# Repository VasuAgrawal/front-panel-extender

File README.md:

# See the associated blog post on my website [here](https://vasuagrawal.com/2025/05/custom-front-panel-extension-pcb/).

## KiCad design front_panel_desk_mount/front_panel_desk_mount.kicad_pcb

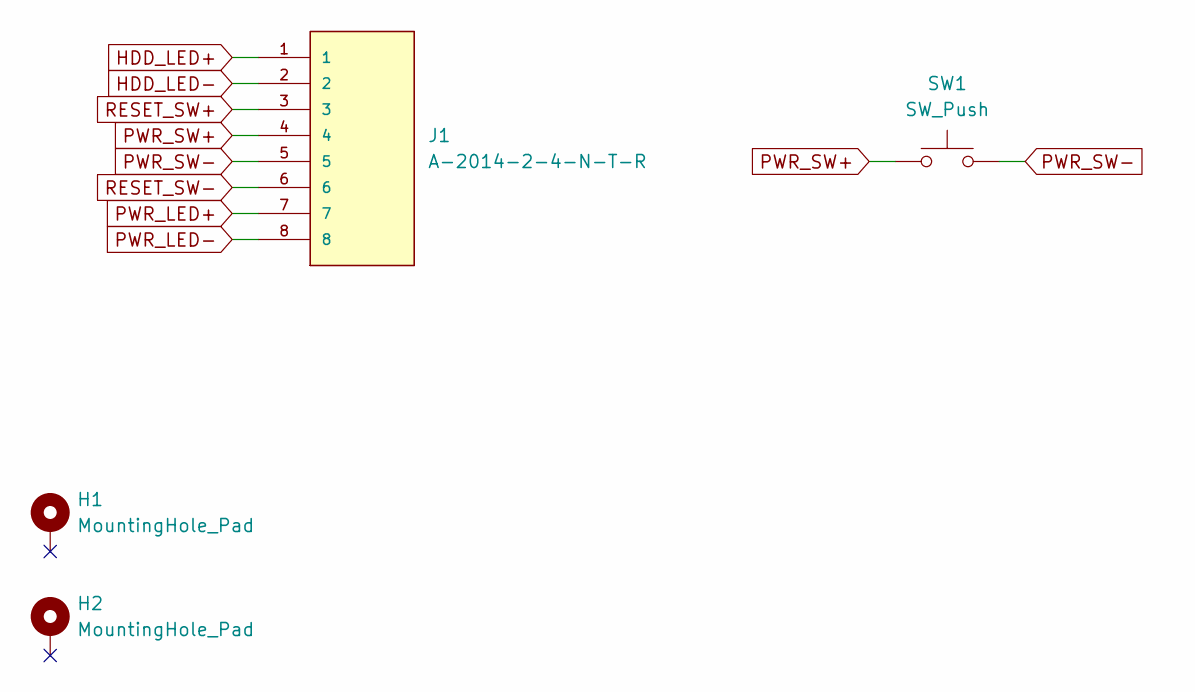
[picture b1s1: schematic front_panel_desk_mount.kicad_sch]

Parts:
H1, H2: MountingHole_Pad; MountingHole_3.2mm_M3_Pad
J1: A-2014-2-4-N-T-R; ASSMANN_A-2014-2-4-N-T-R; PARTREV 01; Digikey AE10396-ND
SW1: SW_Push; SW_Cherry_MX_PCB_1.00u

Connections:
HDD_LED+: J1.1
HDD_LED-: J1.2
PWR_LED+: J1.7
PWR_LED-: J1.8
PWR_SW+: J1.4, SW1.1
PWR_SW-: J1.5, SW1.2
RESET_SW+: J1.3
RESET_SW-: J1.6

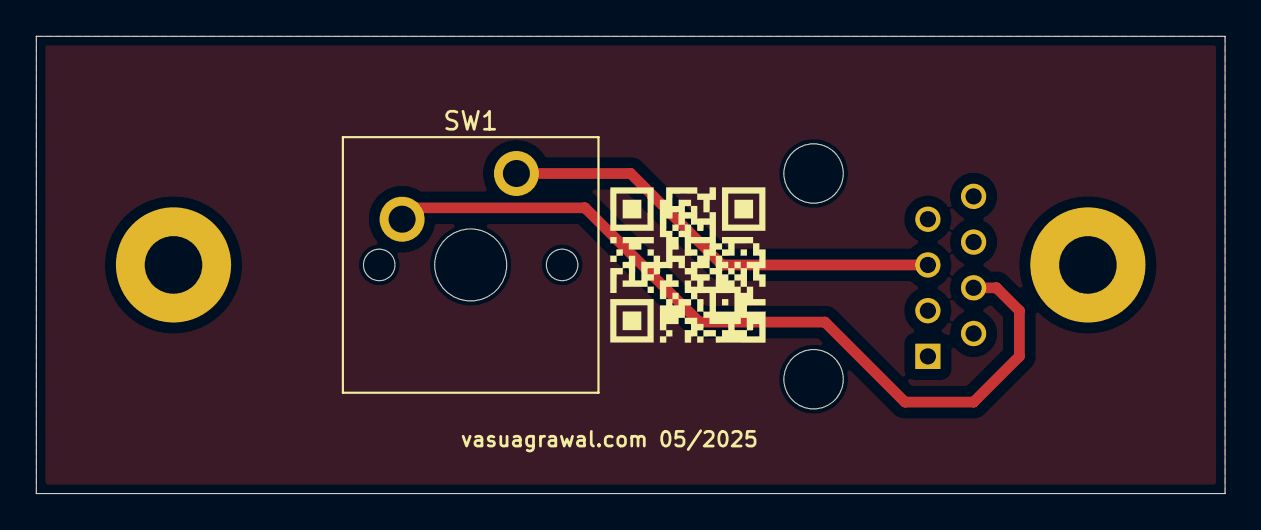
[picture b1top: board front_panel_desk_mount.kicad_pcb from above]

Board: 2 copper layers, 66.0 x 25.4 mm, 4 parts (1 on the bottom side), 2 nets.

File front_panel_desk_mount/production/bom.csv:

Designator,Footprint,Quantity,Value,LCSC Part #
J1,ASSMANN_A-2014-2-4-N-T-R,1,A-2014-2-4-N-T-R,
SW1,SW_Cherry_MX_PCB_1.00u,1,SW_Push,

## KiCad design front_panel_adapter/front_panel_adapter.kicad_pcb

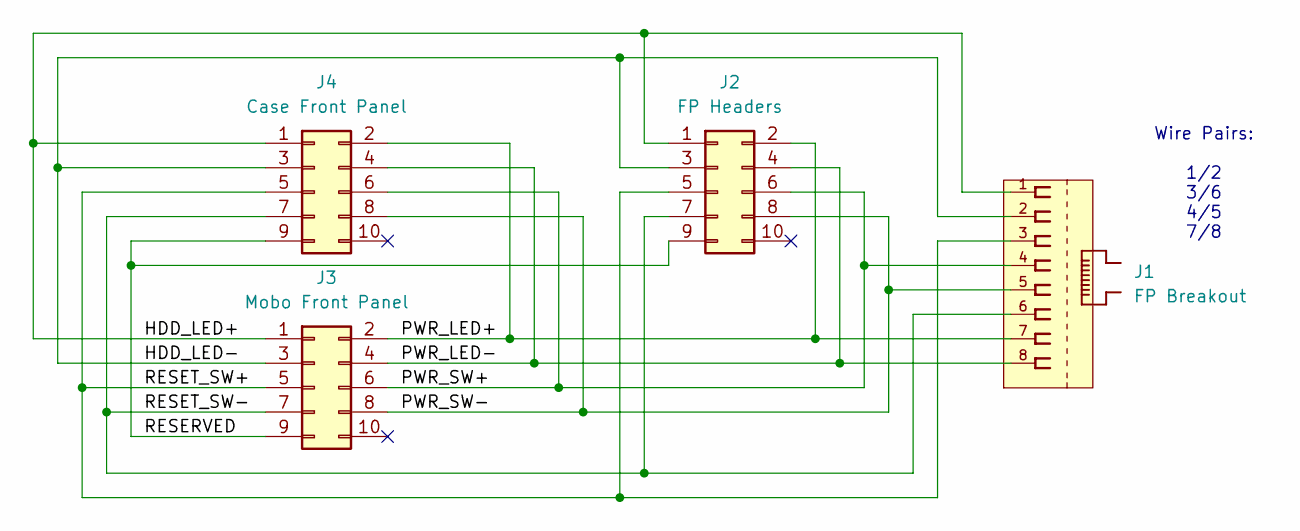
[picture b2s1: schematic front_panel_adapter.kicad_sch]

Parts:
J1: FP Breakout; AMPHENOL_54602-908LF; PARTREV J; DigiKey 609-1046-ND
J2: FP Headers; PinHeader_2x05_P2.54mm_Vertical; DigiKey 1849-1002-ND
J3: Mobo Front Panel; PinSocket_2x05_P2.54mm_Vertical; DigiKey 4324-FHMD-DA010G1NBON-B-ND
J4: Case Front Panel; PinHeader_2x05_P2.54mm_Vertical; DigiKey 1849-1002-ND

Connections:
/HDD_LED+: J1.1, J2.1, J3.1, J4.1
/HDD_LED-: J1.2, J2.3, J3.3, J4.3
/PWR_LED+: J1.7, J2.2, J3.2, J4.2
/PWR_LED-: J1.8, J2.4, J3.4, J4.4
/PWR_SW+: J1.4, J2.6, J3.6, J4.6
/PWR_SW-: J1.5, J2.8, J3.8, J4.8
/RESERVED: J2.9, J3.9, J4.9
/RESET_SW+: J1.3, J2.5, J3.5, J4.5
/RESET_SW-: J1.6, J2.7, J3.7, J4.7

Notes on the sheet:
Wire Pairs: 1/2 3/6 4/5 7/8

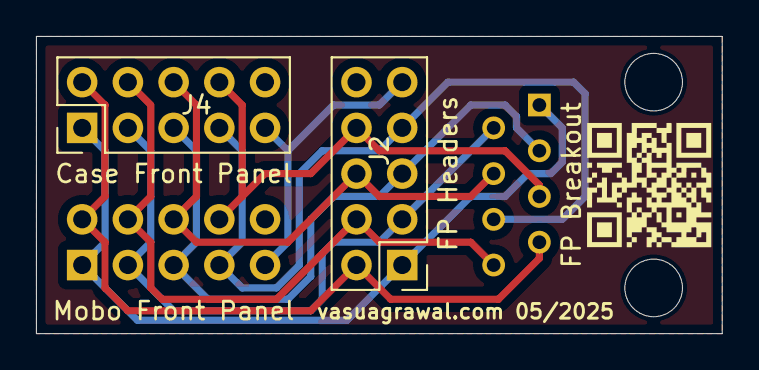
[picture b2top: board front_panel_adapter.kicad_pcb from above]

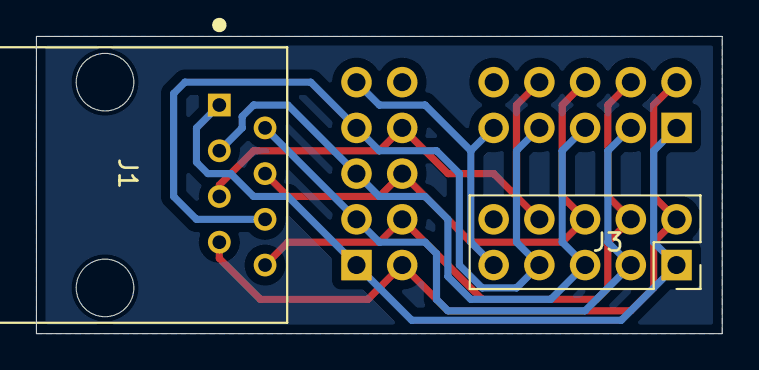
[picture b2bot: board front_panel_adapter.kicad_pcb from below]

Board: 2 copper layers, 38.1 x 16.5 mm, 4 parts (2 on the bottom side), 9 nets.

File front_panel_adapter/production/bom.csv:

Designator,Footprint,Quantity,Value,LCSC Part #
J1,AMPHENOL_54602-908LF,1,FP Breakout,C2847314
J2,PinHeader_2x05_P2.54mm_Vertical,1,FP Headers,
J3,PinSocket_2x05_P2.54mm_Vertical,1,Mobo Front Panel,
J4,PinHeader_2x05_P2.54mm_Vertical,1,Case Front Panel,

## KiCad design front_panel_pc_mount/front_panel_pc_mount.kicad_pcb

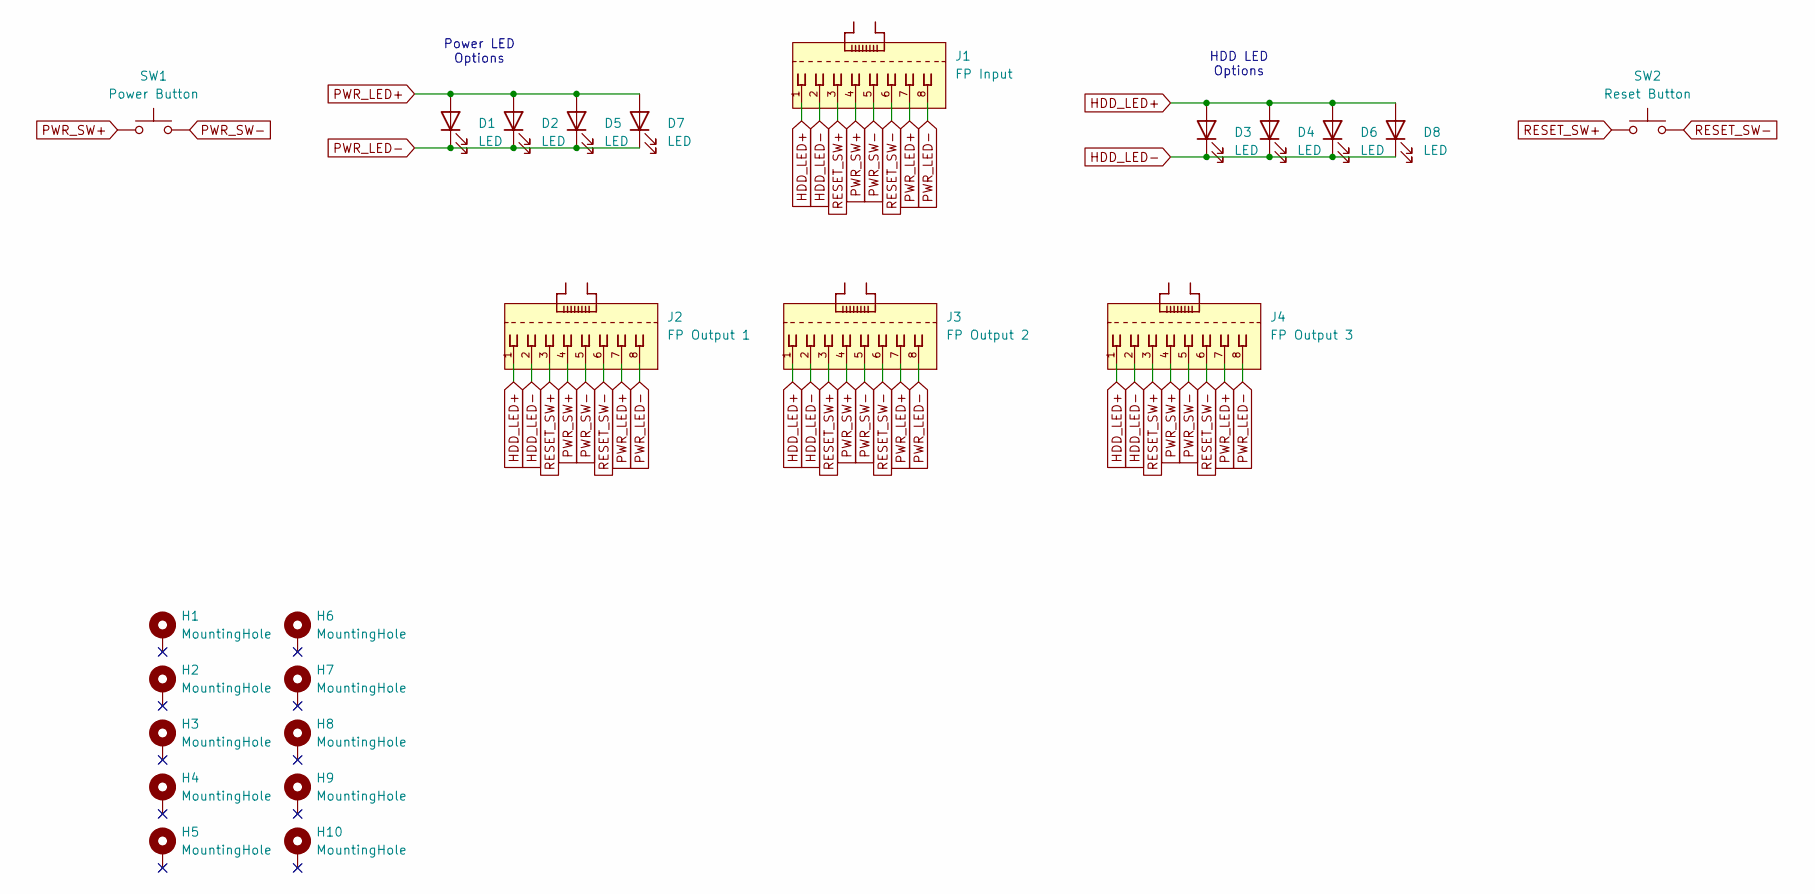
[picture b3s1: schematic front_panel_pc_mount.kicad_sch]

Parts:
D1, D3: LED; LED_D3.0mm
D2, D4: LED; LED_D5.0mm
D5, D6: LED; LED_0603_1608Metric_Pad1.05x0.95mm_HandSolder
D7, D8: LED; LED_0805_2012Metric_Pad1.15x1.40mm_HandSolder
H1, H2, H3, H4, H5, H6, H7, H8, H9, H10: MountingHole; MountingHole_3.2mm_M3_Pad
J1: FP Input; AMPHENOL_54602-908LF; PARTREV J
J2: FP Output 1; AMPHENOL_54602-908LF; PARTREV J
J3: FP Output 2; AMPHENOL_54602-908LF; PARTREV J
J4: FP Output 3; AMPHENOL_54602-908LF; PARTREV J
SW1: Power Button; SW_Cherry_MX_PCB_1.00u
SW2: Reset Button; SW_Cherry_MX_PCB_1.00u

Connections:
HDD_LED+: D3.2 (A), D4.2 (A), D6.2 (A), D8.2 (A), J1.1, J2.1, J3.1, J4.1
HDD_LED-: D3.1 (K), D4.1 (K), D6.1 (K), D8.1 (K), J1.2, J2.2, J3.2, J4.2
PWR_LED+: D1.2 (A), D2.2 (A), D5.2 (A), D7.2 (A), J1.7, J2.7, J3.7, J4.7
PWR_LED-: D1.1 (K), D2.1 (K), D5.1 (K), D7.1 (K), J1.8, J2.8, J3.8, J4.8
PWR_SW+: J1.4, J2.4, J3.4, J4.4, SW1.1
PWR_SW-: J1.5, J2.5, J3.5, J4.5, SW1.2
RESET_SW+: J1.3, J2.3, J3.3, J4.3, SW2.1
RESET_SW-: J1.6, J2.6, J3.6, J4.6, SW2.2

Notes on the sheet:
Power LED Options
HDD LED Options

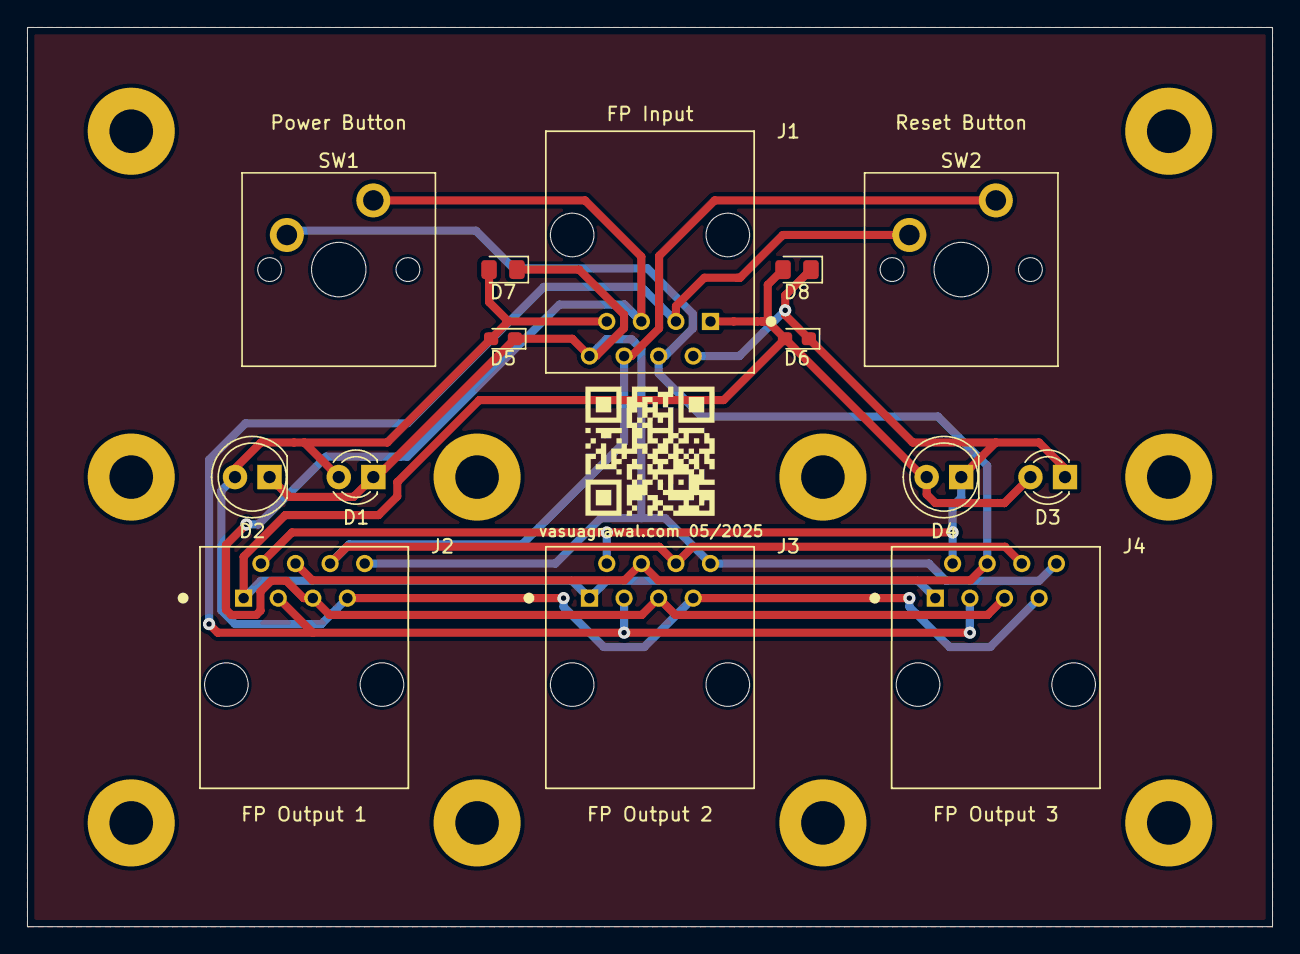
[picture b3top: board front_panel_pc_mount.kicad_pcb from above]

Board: 2 copper layers, 91.4 x 66.0 mm, 24 parts (0 on the bottom side), 8 nets.

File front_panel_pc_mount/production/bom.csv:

Designator,Footprint,Quantity,Value,LCSC Part #
"D1, D3",LED_D3.0mm,2,LED,
"D2, D4",LED_D5.0mm,2,LED,
"D5, D6",0603,2,LED,
"D7, D8",0805,2,LED,
J1,AMPHENOL_54602-908LF,1,FP Input,
J2,AMPHENOL_54602-908LF,1,FP Output 1,
J3,AMPHENOL_54602-908LF,1,FP Output 2,
J4,AMPHENOL_54602-908LF,1,FP Output 3,
SW1,SW_Cherry_MX_PCB_1.00u,1,Power Button,
SW2,SW_Cherry_MX_PCB_1.00u,1,Reset Button,

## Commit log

2025-06-12 Add gitignore
2025-06-12 Add completed kicad boards
2025-06-12 Add 3D models
2025-06-12 Create LICENSE
